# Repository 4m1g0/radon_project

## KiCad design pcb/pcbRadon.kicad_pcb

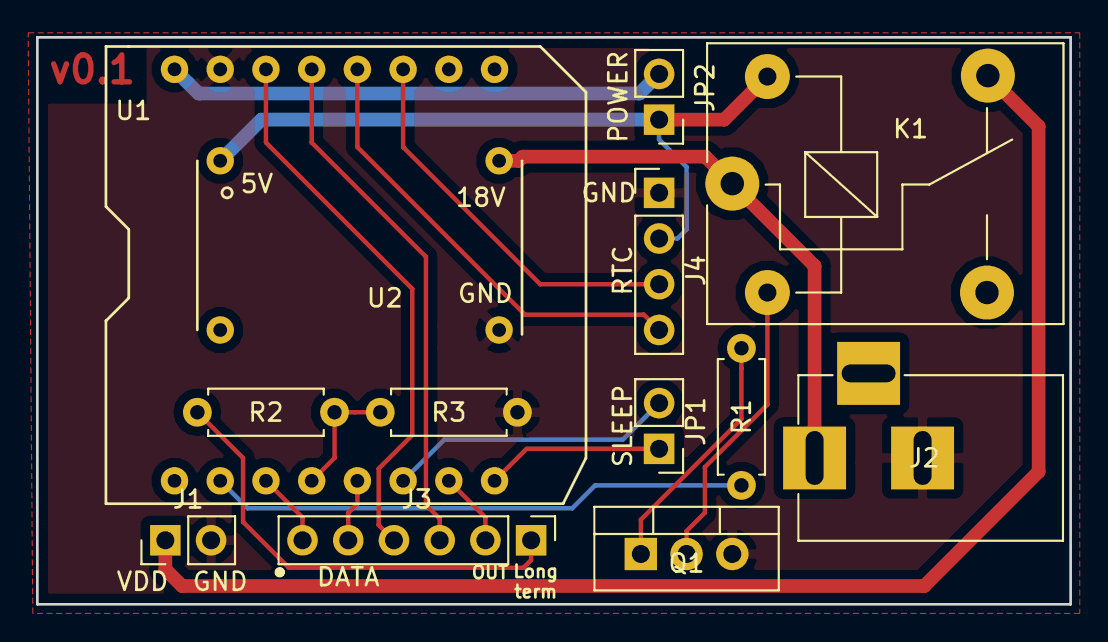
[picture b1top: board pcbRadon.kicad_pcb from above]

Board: 2 copper layers, 57.4 x 31.5 mm, 13 parts (0 on the bottom side), 19 nets.

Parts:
J1: Conn_01x02; Pin_Header_Straight_1x02_Pitch2.54mm
J2: Jack-DC; BARREL_JACK
J3: Conn_01x06; Pin_Header_Straight_1x06_Pitch2.54mm
J4: RTC; Pin_Header_Straight_1x04_Pitch2.54mm
JP1, JP2: Jumper; Pin_Header_Straight_1x02_Pitch2.54mm
K1: SANYOU_SRD_Form_C; Relay_SPDT_SANYOU_SRD_Series_Form_C
Q1: TIP120; TO-220_Vertical
R1, R2: 2K2; R_Axial_DIN0207_L6.3mm_D2.5mm_P7.62mm_Horizontal
R3: 2M2; R_Axial_DIN0207_L6.3mm_D2.5mm_P7.62mm_Horizontal
U1: Wemos; WEMOS_D1_TH
U2: Step-down; Step-Down

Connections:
GND: J1.2, J2.2, J4.1, Q1.3, R3.2, U1.9, U2.4
unnamed: J1.1, K1.4
unnamed: J3.1, R2.2
unnamed: J3.2, U1.1
unnamed: J3.3, U1.11
unnamed: J3.4, U1.10
unnamed: J3.5, U1.3
unnamed: J3.6, U1.5
unnamed: J4.3, U1.13
unnamed: J4.4, U1.12
unnamed: JP1.1, U1.0
unnamed: JP1.2, U1.2
unnamed: JP2.2, U1.8
unnamed: K1.2, Q1.2
unnamed: Q1.1, R1.2
unnamed: R1.1, U1.6
unnamed: R2.1, R3.1, U1.4
VCC: J4.2, JP2.1, K1.5, U2.1
VDD: J2.1, K1.1, U2.3

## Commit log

2018-01-25 Add service in nodejs
2018-02-06 Add sensor endpoints
2018-02-06 Remove mocked parameters
2018-02-07 Fix order of parameters
2018-02-07 Move firmware to subfolder
2018-02-08 Send status as created in post
2018-02-09 Add firmware implementation
2018-02-12 Add delete endpoint for testing pruposes
2018-02-15 Check for errors in ntp response in the Clock library and fix reset pin for deepsleep
2018-02-27 Change to short term when reading value
2018-03-02 Fix digit 6 recognition
2018-05-29 Request reset if value < 0 (error)
2018-05-29 Add reset capabilities and autoupdate
2018-07-11 Añadidos archivos de PCB
2018-07-18 Add modification for the new sesor and included the user interface
2018-07-19 Add Daily stats component
2018-07-26 Add Alerts, still need backend
2018-07-27 Add CORS headers0
2018-07-27 Add alert endpoints
2018-07-27 Add get Alerts endpoint
2018-07-27 Add atob to the packages and fix some error in api
2018-07-27 Add api calls for alerts
2018-11-27 Add Kicad PCB files
2018-11-27 Fixed connection to relay (normaly close) and add silkscreen texts
2018-12-13 Change network and obtain the time throught the service instead of ntp, to avoid problems with the firewall
2018-12-13 Add endpoint to get the time through the Service
2018-12-13 Use chip id as sensor identifier and also use it to select the update package
